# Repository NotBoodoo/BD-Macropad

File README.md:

# BD-Macropad

I wanted to create a macropad that has lot keys, as many as possible. I created a macropad using 12 switches, 1 rp2040, 1 rotary encoder, and 1 Oled 128x32 display.

### Challenges

I used QMK firmware. Firmware was the hardest part. I was constantly having errors while compiling. But after few days of trying i barely managed to compile. But i don't even know it will work or not.
 
### Specifications

BOM: 
- 12x Cherry MX Switches
- 1x XIAO RP2040
- 1x EC11 Rotary encoder
- 1x 0.91 inch OLED display
- 12x Through-hole 1N4148 Diodes
- 12x Blank DSA Keycaps
- 4x M3x6 Bolt
- 4x M3 Heatset

Others:
- QMK Firmware
- Top_Shell.step 
- Bottom_Shell.step
- Knob.step

Schematic            |  PCB         |   Case
:-------------------------:|:-------------------------:|:-------------------------:|
    |    |

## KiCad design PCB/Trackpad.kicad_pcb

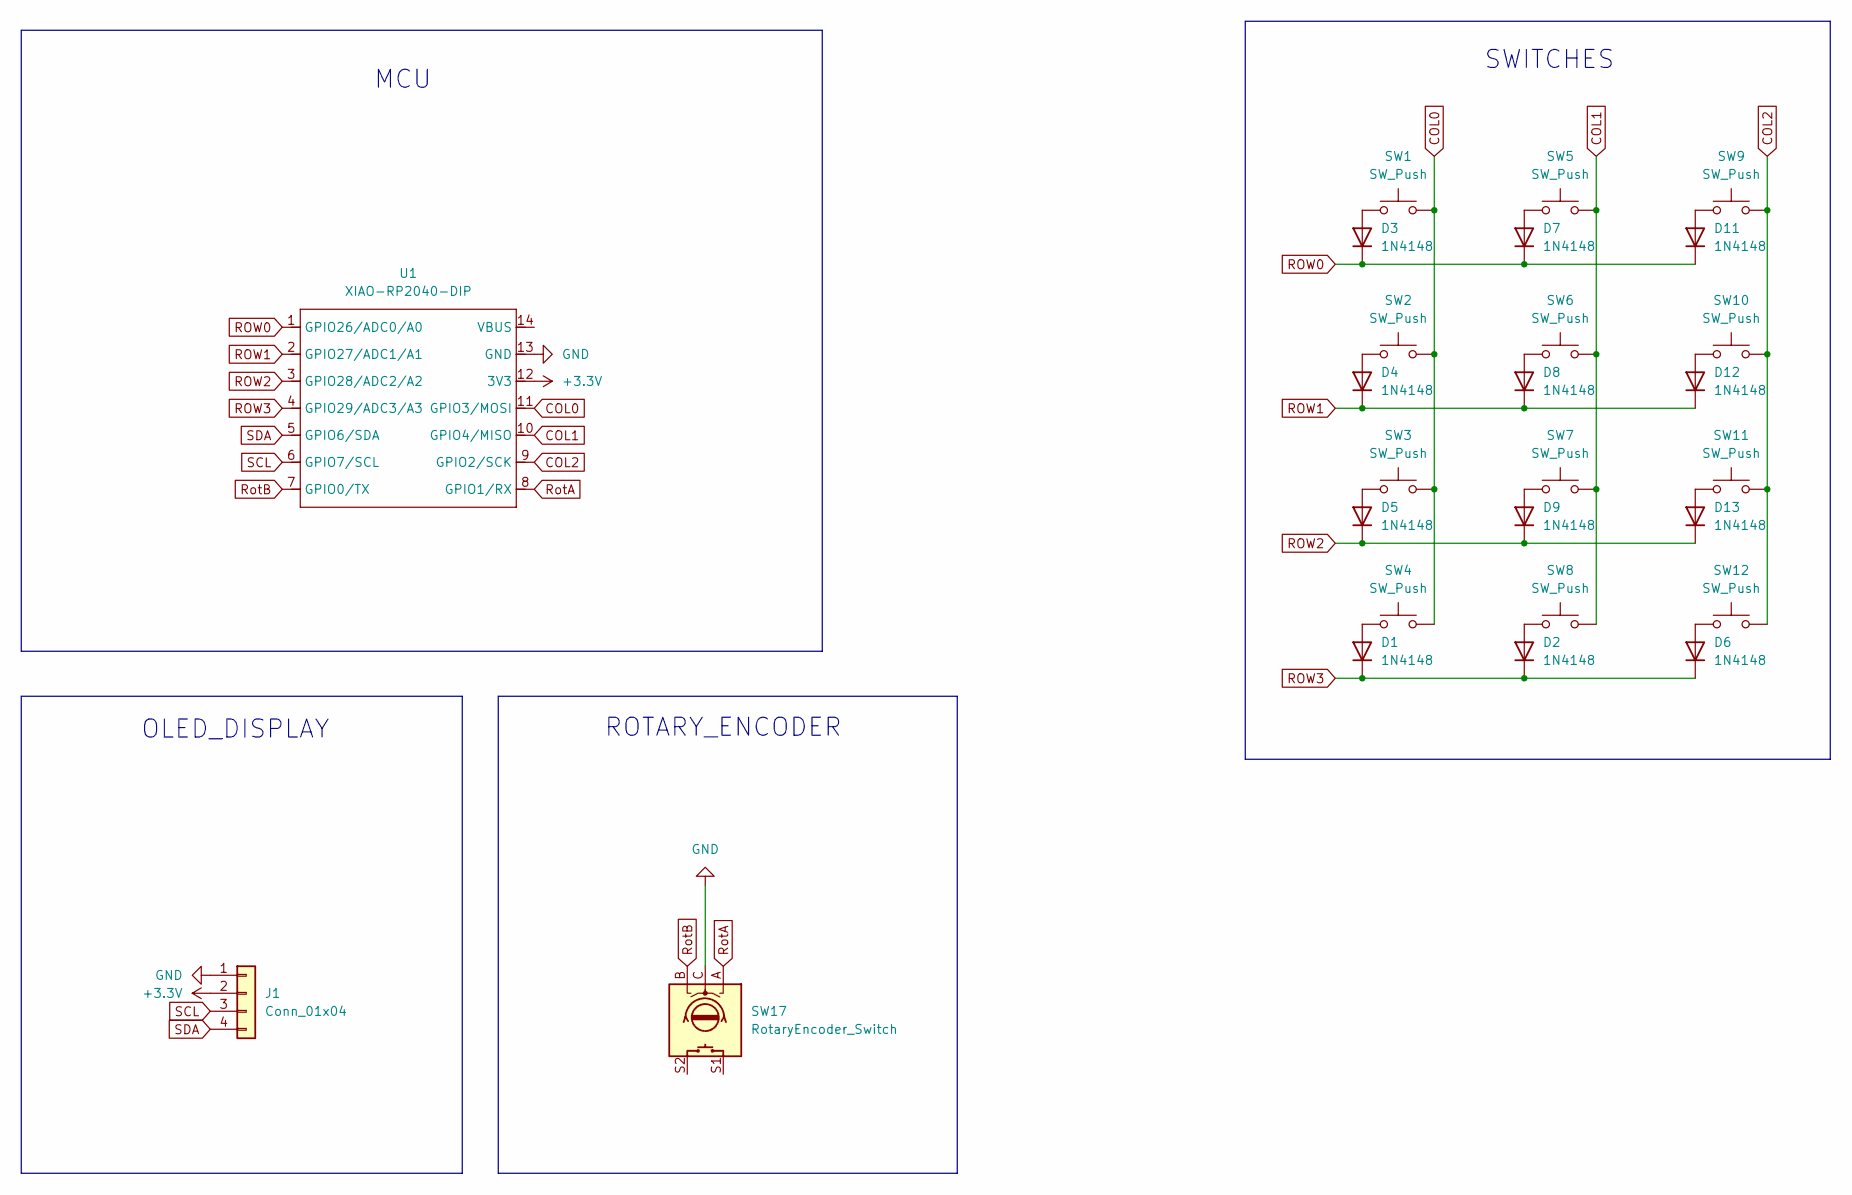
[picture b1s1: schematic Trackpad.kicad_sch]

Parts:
D1, D2, D3, D4, D5, D6, D7, D8, D9, D11, D12, D13: 1N4148; D_DO-35_SOD27_P7.62mm_Horizontal
J1: Conn_01x04; SSD1306-0.91-OLED-4pin-128x32
SW1, SW2, SW3, SW4, SW5, SW6, SW7, SW8, SW9, SW10, SW11, SW12: SW_Push; SW_Cherry_MX_1.00u_PCB
SW17: RotaryEncoder_Switch; RotaryEncoder_Alps_EC11E-Switch_Vertical_H20mm
U1: XIAO-RP2040-DIP

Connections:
+3.3V: J1.2, U1.12 (3V3)
COL0: SW1.2, SW2.2, SW3.2, SW4.2, U1.11 (GPIO3/MOSI)
COL1: SW5.2, SW6.2, SW7.2, SW8.2, U1.10 (GPIO4/MISO)
COL2: SW9.2, SW10.2, SW11.2, SW12.2, U1.9 (GPIO2/SCK)
GND: J1.1, SW17.C, U1.13 (GND)
unnamed: D1.2 (A), SW4.1
unnamed: D2.2 (A), SW8.1
unnamed: D3.2 (A), SW1.1
unnamed: D4.2 (A), SW2.1
unnamed: D5.2 (A), SW3.1
unnamed: D6.2 (A), SW12.1
unnamed: D7.2 (A), SW5.1
unnamed: D8.2 (A), SW6.1
unnamed: D9.2 (A), SW7.1
unnamed: D11.2 (A), SW9.1
unnamed: D12.2 (A), SW10.1
unnamed: D13.2 (A), SW11.1
ROW0: D3.1 (K), D7.1 (K), D11.1 (K), U1.1 (GPIO26/ADC0/A0)
ROW1: D4.1 (K), D8.1 (K), D12.1 (K), U1.2 (GPIO27/ADC1/A1)
ROW2: D5.1 (K), D9.1 (K), D13.1 (K), U1.3 (GPIO28/ADC2/A2)
ROW3: D1.1 (K), D2.1 (K), D6.1 (K), U1.4 (GPIO29/ADC3/A3)
RotA: SW17.A, U1.8 (GPIO1/RX)
RotB: SW17.B, U1.7 (GPIO0/TX)
SCL: J1.3, U1.6 (GPIO7/SCL)
SDA: J1.4, U1.5 (GPIO6/SDA)

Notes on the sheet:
MCU
SWITCHES
ROTARY_ENCODER
OLED_DISPLAY

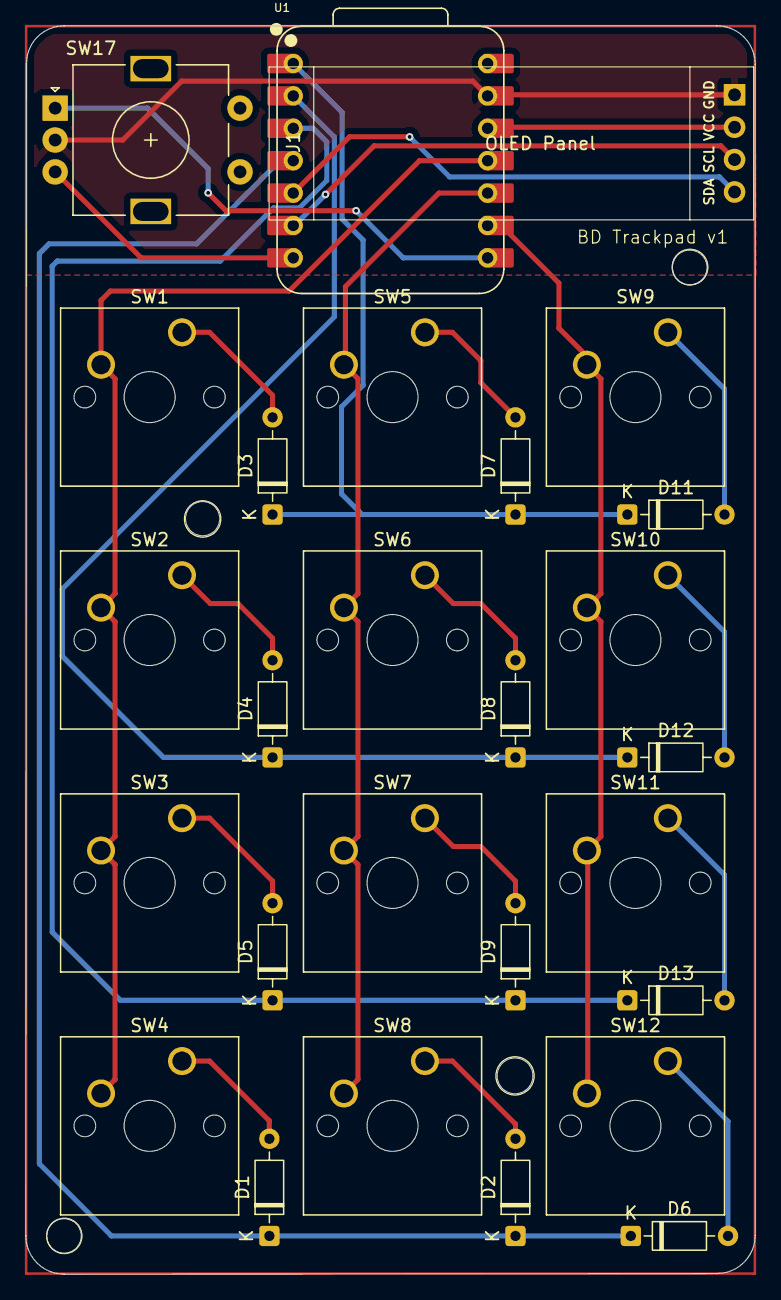
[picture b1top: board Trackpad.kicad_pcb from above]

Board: 2 copper layers, 57.2 x 97.9 mm, 27 parts (0 on the bottom side), 25 nets.

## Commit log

2026-01-17 Fix spelling and clarity issues in README.md
    Corrected spelling errors and improved clarity in the README.
